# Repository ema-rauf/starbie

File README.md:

# Starbie

A small motion-controlled desk pet on a custom PCB. A XIAO ESP32-C3 draws a wandering pet on a 0.96" OLED, an MPU6050 reads tilt and shakes, a DHT11 reads temperature and humidity, and two buttons open a radial menu and a stats screen.

Built for Hack Club Half-Life, Week 1 (PCB design). Based on the [Week 1 example project by SharKingStudios](https://github.com/SharKingStudios/Starbie).

## How it works

| Control | What it does |
|---|---|
| Button 1, first press | Opens the radial menu |
| Tilt while the menu is open | Moves the selector ball toward NAP, PLAY, FEED or PET |
| Button 1, second press | Chooses the highlighted action |
| Button 2 | Shows or hides the stats screen (joy, energy, fullness, temperature, humidity) |
| Shake | Gives the pet a shake reaction |

## Parts

| Part | Reference |
|---|---|
| Seeed Studio XIAO ESP32-C3 | U1 |
| 0.96" 128x64 I2C OLED | J1 (4-pin header) |
| MPU6050 module (GY-521) | J2 (8-pin header) |
| DHT11 sensor | U2 |
| 10k resistor (pull-up on DHT11 data) | R1 |
| Push buttons (Cherry MX footprint) | SW1, SW3 |

## Bill of Materials

| Item | Qty | Supplier | Cost/item | Total Cost |
|---|---|---|---|---|
| [XIAO ESP32-C3 (bare, no headers)](https://www.or97.com/product/seeed-studio-xiao-esp32c3-risc-v-tiny-mcu-board-with-wi-fi-and-bluetooth5-0/) | 1 | OR97 | $14.44 | $14.44 |
| [0.96″ I2C OLED](https://digilog.pk/products/arduino-0-96-inch-iic-oled-display-128x64-i2c-ssd1306-lcd-screen-in-pakistan) | 1 | Digilog | $1.79 | $1.79 |
| [DHT11](https://digilog.pk/products/dht11-temperature-humidity-sensor-module-for-arduino) | 1 | Digilog | $1.00 | $1.00 |
| [10k resistor](https://digilog.pk/products/resistor-1-pack-of-15-value-10r-47r-100r-220r-330r-470r-1k-2-2k-4-7k-6-8k-10k-22k-47k-100k-220k-1) | 1 | Digilog | $1.00 | $1.00 |
| [2.54 mm male header strip](https://digilog.pk/products/gold-plated-2-54mm-male-40-pin-single-row-straight-round-pin-header-strip-in-pakistan) | 1 | Digilog | $0.50 | $0.50 |
| [MX-style mechanical switches](https://www.daraz.pk/catalog/?q=MX+mechanical+keyboard+switch) | 1 | Daraz | $1.00 | $1.00 |
| [Soldering iron](https://digilog.pk/products/variable-soldering-iron-093d) | 1 | Digilog | $3.79 | $3.79 |
| [0.8 mm 2.5 ft solder wire](https://digilog.pk/products/0-8mm-dia-2-5-ft-solder-wire-in-pakistan) | 1 | Digilog | $0.20 | $0.20 |
| Estimated total shipping | 1 | | | $6.00 |
| **Total** | | | | **$29.72** |

The same list is in [BOM.csv](BOM.csv).

## Wiring

| XIAO pin | GPIO | Net |
|---|---|---|
| D1 | 3 | DHT11_DATA |
| D2 | 4 | GPIO2 (button 1) |
| D3 | 5 | GPIO3 (button 2) |
| D4 | 6 | SCL (OLED and MPU6050) |
| D5 | 7 | SDA (OLED and MPU6050) |

The OLED and the MPU6050 share the same two I2C lines. The ground net is a copper pour on both layers.

## Firmware

`Starbie/Firmware/Starbie/Starbie.ino` is the example sketch from the guide with one change: because this board has SCL on D4 and SDA on D5, the I2C pins are set to `I2C_SDA_PIN = 7` and `I2C_SCL_PIN = 6`.

### Building it

1. Install Arduino IDE and add the ESP32 board package (esp32 by Espressif Systems).
2. Install the libraries: Adafruit GFX Library, Adafruit SSD1306, Adafruit MPU6050, DHT sensor library.
3. Select the board **XIAO_ESP32C3** and click **Verify/Compile**.

The sketch compiles (26% of program storage, 4% of dynamic memory). It has not been uploaded to hardware yet, because the board has not been built.

## Repository layout

| Path | Contents |
|---|---|
| `Starbie/` | KiCad project (`.kicad_pro`, `.kicad_sch`, `.kicad_pcb`) |
| `Starbie/Gerbers/` | Gerber and drill files for manufacturing |
| `Starbie/Firmware/Starbie/` | Arduino sketch |
| `Week 1 Care Package/` | Symbol and footprint libraries and 3D models used by the project |
| `BOM.csv` | Bill of materials with prices |
| `JOURNAL.md` | Build journal |

## Status

The PCB is designed and routed. The design rules check shows no unconnected items. The only 2 errors are "malformed courtyard" errors on the OLED footprint (J1) that come from the care package footprint.

## Screenshots

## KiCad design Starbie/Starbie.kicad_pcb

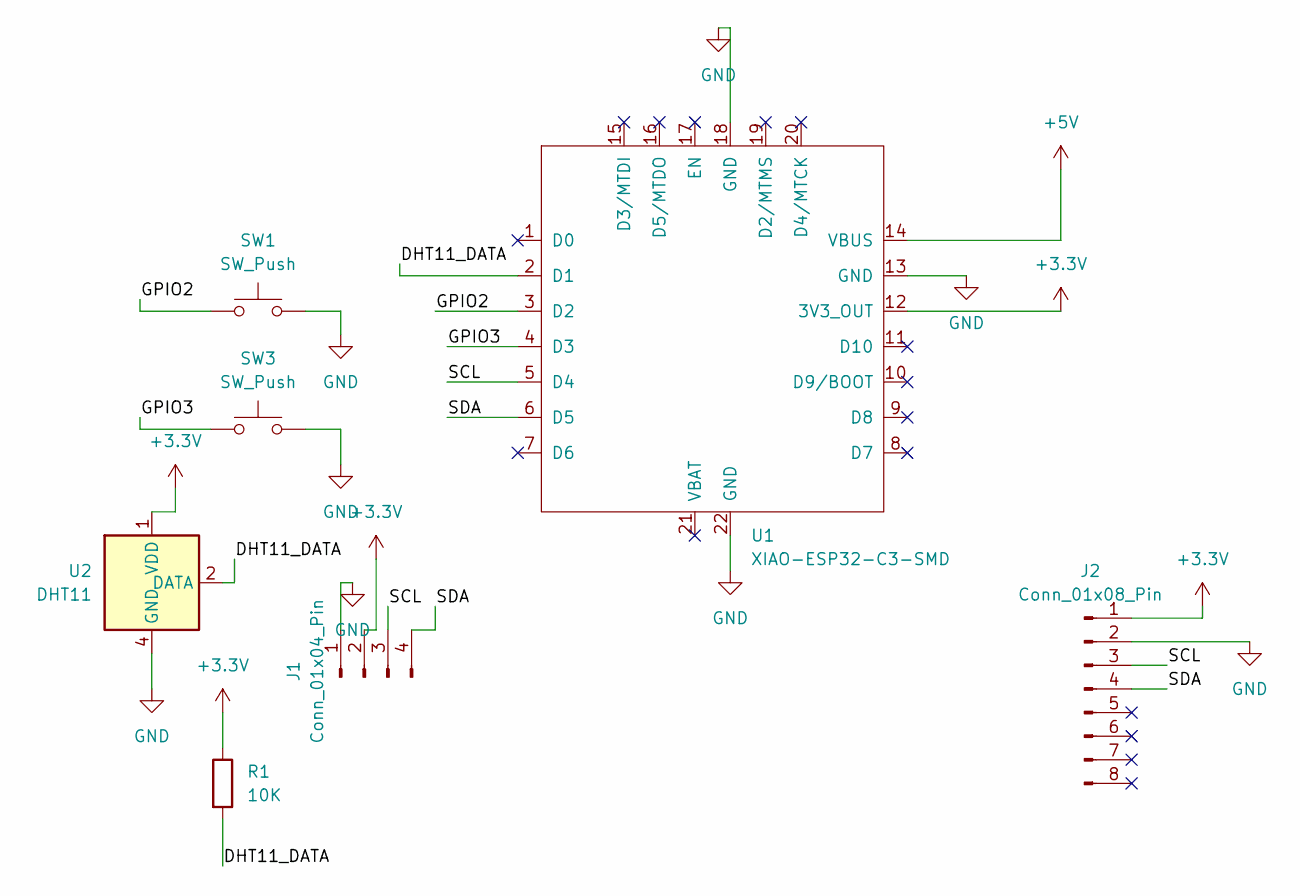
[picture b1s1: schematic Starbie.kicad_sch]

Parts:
J1: Conn_01x04_Pin; Display_128x64_096_I2C
J2: Conn_01x08_Pin; PinHeader_1x08_P2.54mm_Vertical
R1: 10K; R_Axial_DIN0204_L3.6mm_D1.6mm_P7.62mm_Horizontal
SW1, SW3: SW_Push; SW_Cherry_MX_1.00u_PCB
U1: XIAO-ESP32-C3-SMD
U2: DHT11; Aosong_DHT11_5.5x12.0_P2.54mm

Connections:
+3.3V: J1.2, J2.1, R1.1, U1.12 (3V3_OUT), U2.1 (VDD)
+5V: U1.14 (VBUS)
/DHT11_DATA: R1.2, U1.2 (D1), U2.2 (DATA)
/GPIO2: SW1.1, U1.3 (D2)
/GPIO3: SW3.1, U1.4 (D3)
/SCL: J1.3, J2.3, U1.5 (D4)
/SDA: J1.4, J2.4, U1.6 (D5)
GND: J1.1, J2.2, SW1.2, SW3.2, U1.13 (GND), U1.18 (GND), U1.22 (GND), U2.4 (GND)

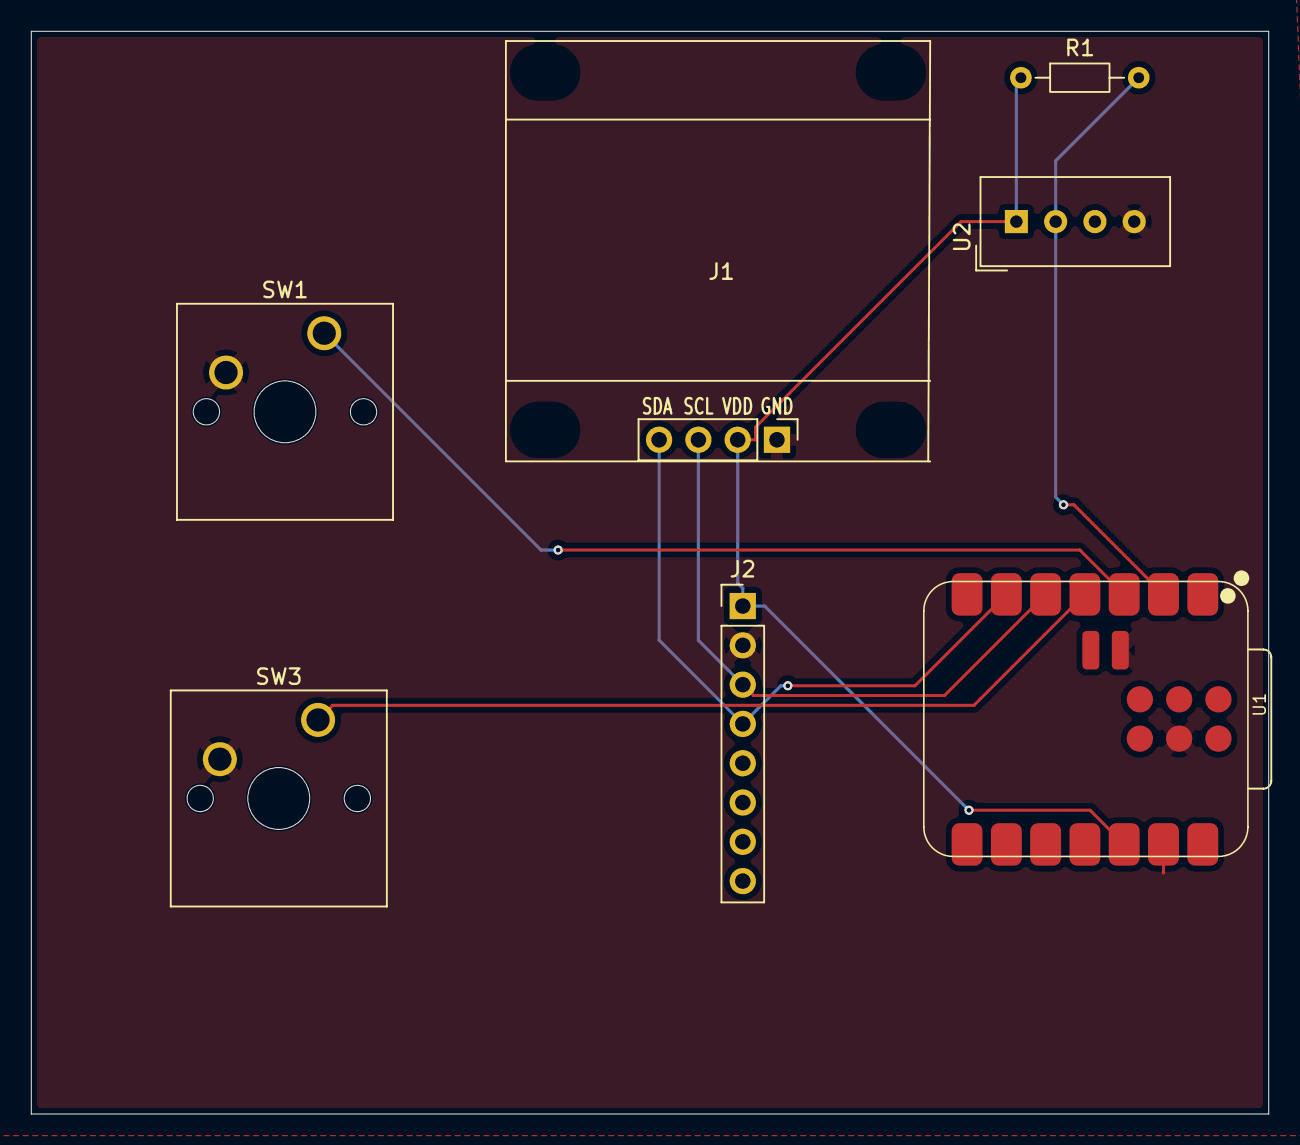
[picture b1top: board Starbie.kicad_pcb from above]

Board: 2 copper layers, 80.0 x 70.0 mm, 7 parts (0 on the bottom side), 7 nets.
